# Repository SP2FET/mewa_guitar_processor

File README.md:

# mewa_guitar_processor
Used libraries:
https://mega.nz/folder/YqhwTCiK#ghKgNH-lcBZVIpoeHB-dDw

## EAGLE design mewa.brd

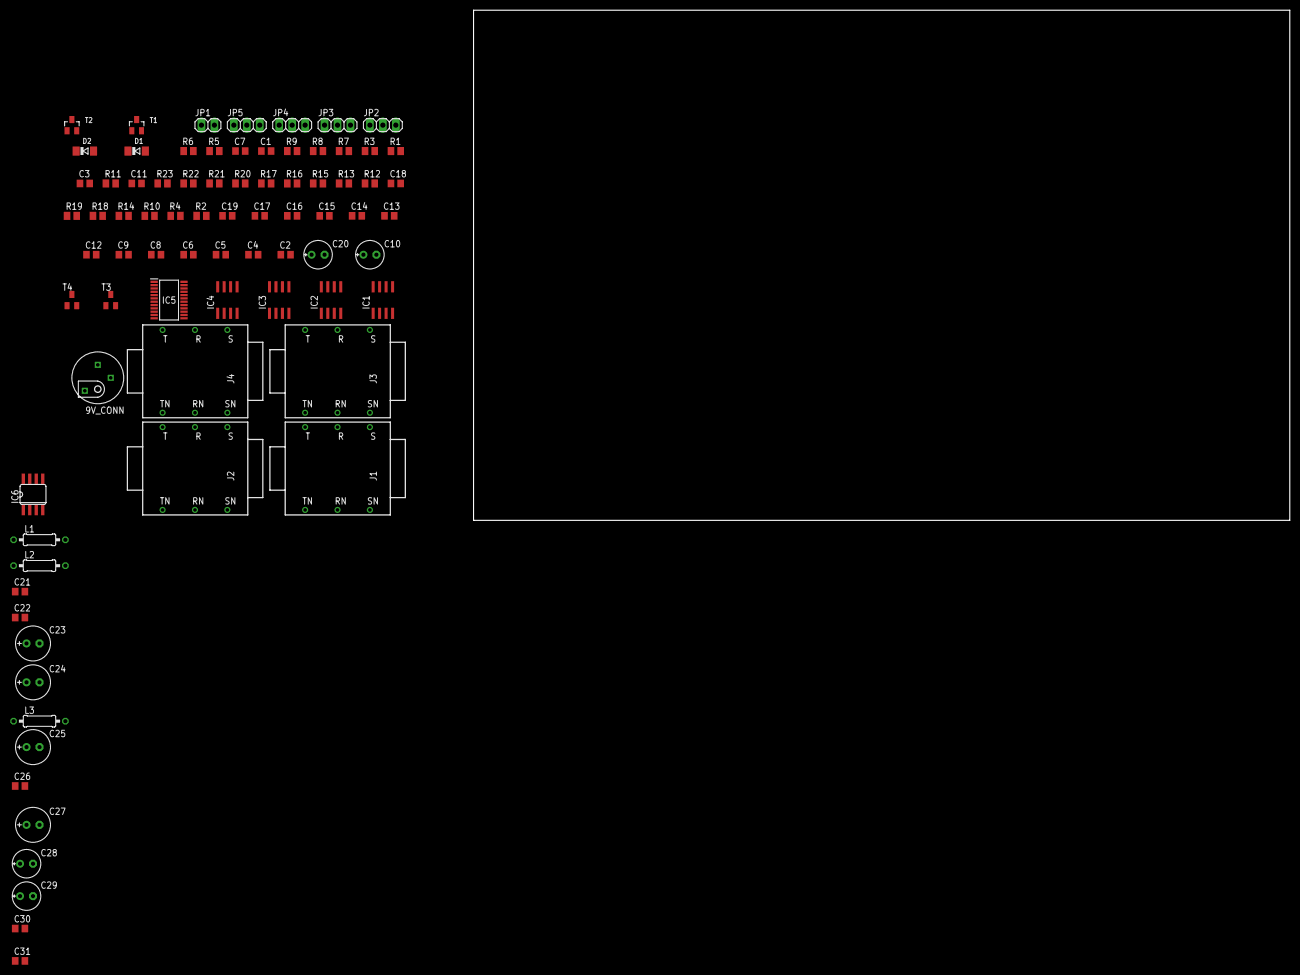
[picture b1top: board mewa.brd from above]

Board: 2 copper layers, 160.0 x 100.0 mm, 79 parts (0 on the bottom side), 48 nets, no tracks yet.

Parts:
9V_CONN: BOSS_JACK
C1, C7, C11, C18: 1n; C0805
C2, C8, C12, C19: 470p; C0805
C3: 47n; C0805
C4, C5, C6, C13, C14, C15, C16, C17, C21, C22, C26: 100n; C0805
C9: 100p; C0805
C10, C20, C28, C29: 10u; E2,5-6E
C23: 470u; E2,5-7
C24, C25: 100u; E2,5-7
C27: 10u; E2,5-7
C30, C31: 1u FILM; C0805
D1, D2: PMLL4148L; SOD80C
IC1, IC2, IC3, IC4: TL072D; SO08
IC5: CS4270-CZZR; SOP65P640X120-24N
IC6: ICL7660CSA; SO08
J1, J2, J3, J4: STEREOSW; NMJ6HCD2
JP1: 1X02
JP2, JP3, JP4, JP5: 1X03
L1, L2, L3: 100u; 0207/10
R1, R9, R13, R17: 12k; M0805
R2, R10, R14, R18, R19: 8.2k; M0805
R3, R20, R21: 10k; M0805
R4: 5.2k; M0805
R5, R15, R22, R23: 1k; M0805
R6, R16: 1M; M0805
R7, R8, R11, R12: 20k; M0805
T1, T2: PDTA114ET; SOT23
T3, T4: BC847; SOT23

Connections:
#MUTEA: IC5.21, T1.1
#MUTEB: IC5.24, T2.1
+AVCC: C4.2, C14.2, C16.2, C25.+, C26.1, D1.1, IC1.8, IC2.8, IC3.8, L2.2, T1.2, T2.2
-AVCC: C5.2, C15.2, C17.2, C29.-, C31.1, D2.2, IC1.4, IC2.4, IC3.4, L3.2
CODEC_IN_A: C1.2, IC1.6, IC1.7, IC5.15
CODEC_IN_B: C11.2, IC3.6, IC3.7, IC5.16
CODEC_OUT_A: IC5.22, R9.1
CODEC_OUT_B: IC5.23, R17.1
GND: 9V_CONN.SLEEVE, C2.1, C4.1, C5.1, C6.1, C8.1, C12.1, C14.1, C15.1, C16.1, C17.1, C19.1, C21.2, C22.2, C23.-, C24.-, C25.-, C26.2, C28.+, C29.+, C30.2, C31.2, IC2.3, IC6.3, J1.R, J1.S, J1.TN, J2.R, J2.S, J3.S, J4.S, JP1.1, JP2.3, JP3.3, JP4.3, JP5.3, R6.1, R16.1, R19.1, R20.1, R21.1, T3.2, T4.2
unnamed: C1.1, R1.2, R2.1
unnamed: IC1.1, R1.1, R3.2
unnamed: C2.2, IC1.5, R2.2
unnamed: C6.2, J1.RN, R7.1, R8.2
unnamed: IC1.2, R3.1, R4.2
unnamed: JP1.2, R4.1
unnamed: IC1.3, R5.2
unnamed: C3.2, R5.1, R6.2
unnamed: C3.1, J1.T
unnamed: C7.1, R9.2, R10.1
unnamed: C8.2, IC2.5, R10.2
unnamed: C9.1, IC2.2, R11.2, R12.1
unnamed: C9.2, C10.+, IC2.1, R12.2
unnamed: C10.-, JP2.1
unnamed: J3.T, JP3.1, JP4.1
unnamed: 9V_CONN.PIN, C21.1, C23.+, L1.1
unnamed: C11.1, R13.2, R14.1
unnamed: J2.TN, J3.TN
unnamed: C12.2, IC3.5, R14.2
unnamed: IC3.1, IC3.2, R13.1
unnamed: C13.1, R15.1
unnamed: D1.2, D2.1, IC3.3, R15.2, R16.2
unnamed: C13.2, JP3.2, JP4.2
unnamed: C18.1, R17.2, R18.1
unnamed: C19.2, IC4.5, R18.2
unnamed: C20.-, J4.T, R19.2
unnamed: C27.+, IC6.2
unnamed: C27.-, IC6.4
unnamed: C20.+, IC4.1, IC4.2
unnamed: C28.-, C30.1, IC6.5, L3.1
unnamed: R20.2, R22.2, T1.3
unnamed: R21.2, R23.2, T2.3
unnamed: R22.1, T3.1
unnamed: R23.1, T4.1
OUT_POT: IC4.3, JP5.2, T4.3
SEND_OUT: J2.T, JP2.2, T3.3
T: C7.2, IC2.6, IC2.7, R11.1
TT: C18.2, IC4.6, IC4.7, JP5.1
V+: C22.1, C24.+, IC4.8, IC6.8, L1.2, L2.1

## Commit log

2020-06-09 Added analog part
    Preamp, effect loop, mute control, output stage
2020-06-09 Added DC/DC converters & voltage inverter
    & changed analog ground to AGND
2020-06-09 Fixed ADC signal levels, added testpads
2020-06-12 AA filters topology changed to Bessel, fc=20kHz
2020-06-12 AA in FX loop changed also

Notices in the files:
parts and their libraries:
NXP_60_26022015: This library may be distributed and adapted freely for any purpose, as long as NXP is credited and any new creation is licensed under the same terms.
